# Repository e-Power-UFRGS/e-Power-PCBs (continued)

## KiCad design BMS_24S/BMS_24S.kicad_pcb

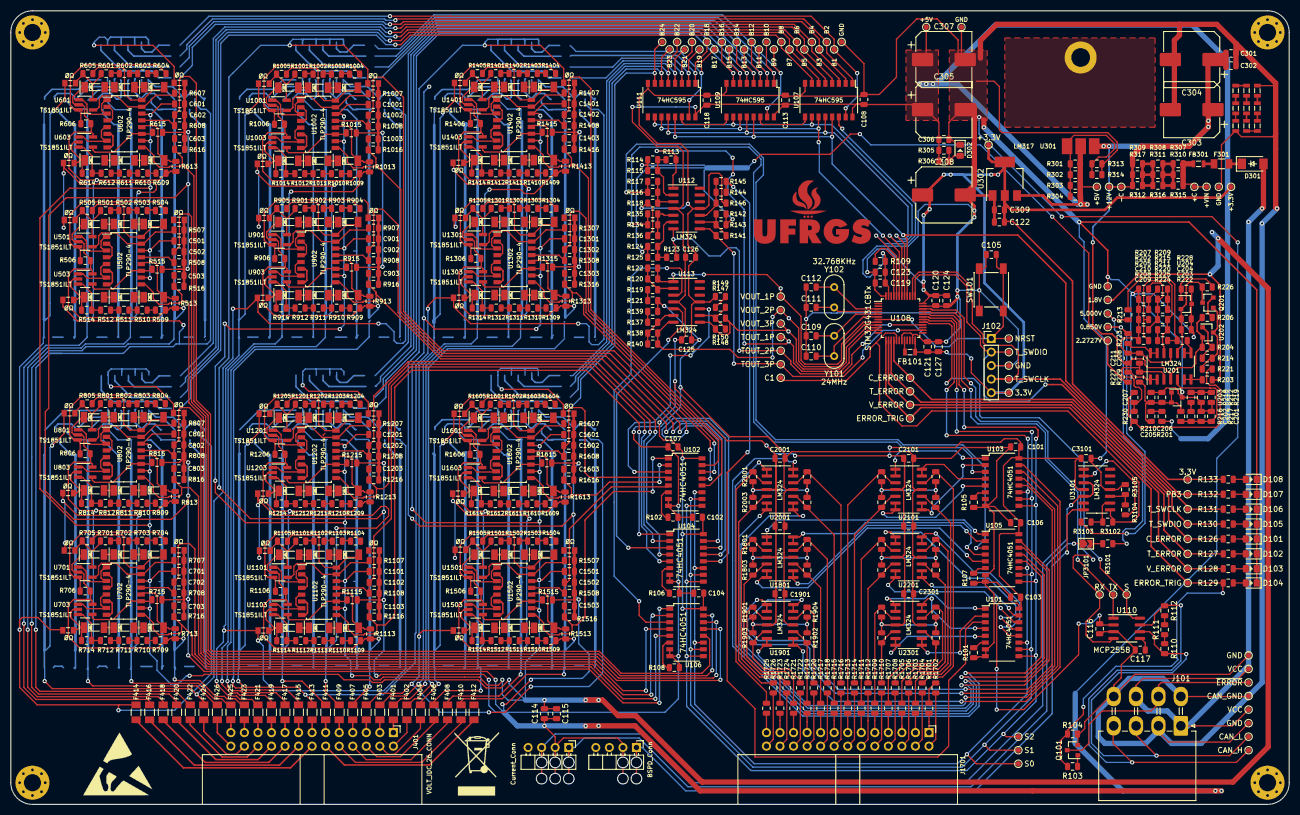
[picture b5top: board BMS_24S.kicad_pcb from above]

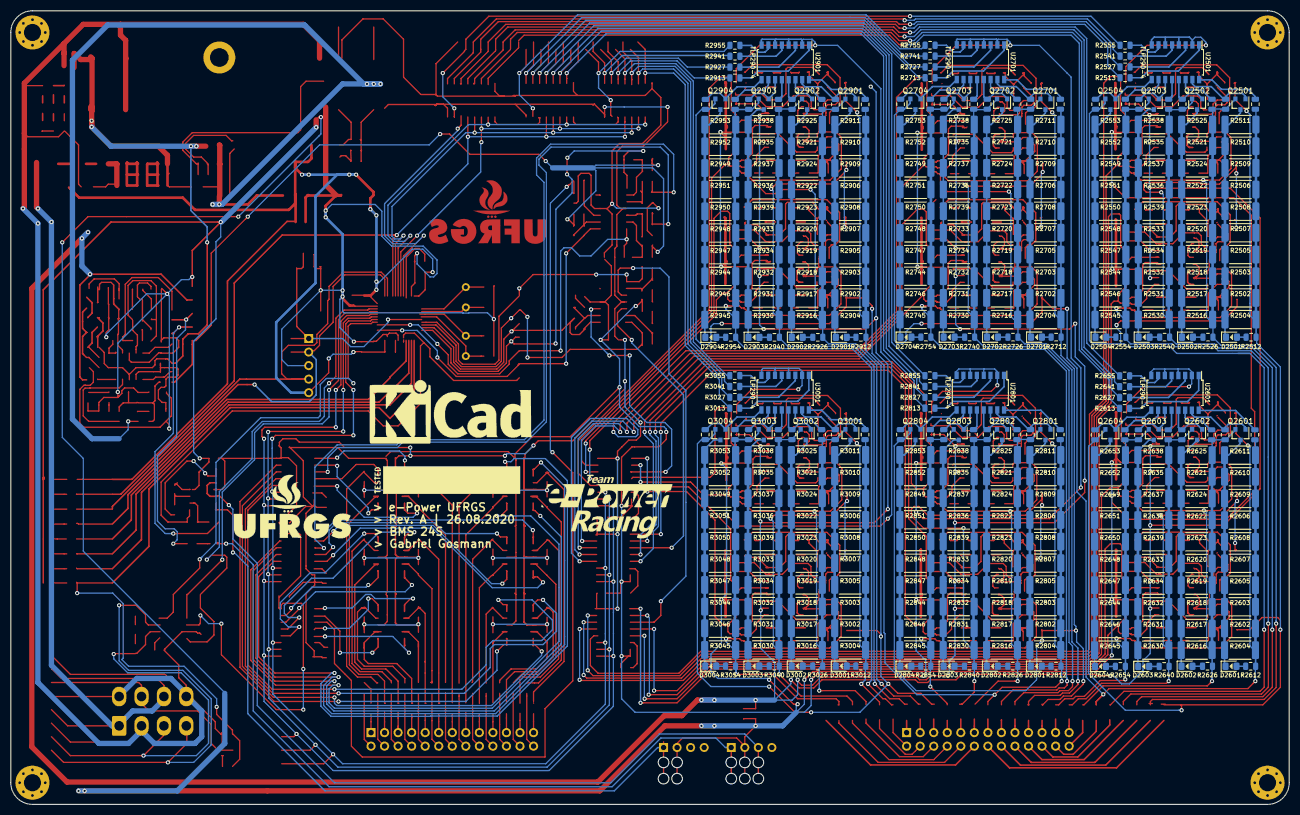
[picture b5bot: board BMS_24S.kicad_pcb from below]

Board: 2 copper layers, 239.8 x 148.8 mm, 1142 parts (393 on the bottom side), 658 nets.

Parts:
C101, C102, C103, C104, C105, C106, C107, C108, C113, C115, C116, C117, C118, C119, C120, C121, C122, C125, C126, C201, C204, C206, C207, C209, C211, C301, C306, C309, C501, C502, C503, C601, C602, C603, C701, C702, C703, C801, C802, C803, C901, C902, C903, C1001, C1002, C1003, C1101, C1102, C1103, C1201, C1202, C1203, C1301, C1302, C1303, C1401, C1402, C1403, C1501, C1502, C1503, C1601, C1602, C1603, C1801, C1901, C2001, C2101, C2201, C2301, C3101: 100nF; C_0805_2012Metric
C109, C110: 12pF; C_0805_2012Metric
C111, C112: 100pF; C_0805_2012Metric
C114, C123, C124, C127, C202, C203, C205, C208, C210, C302: 10uF; C_0805_2012Metric
C303, C304, C305, C307, C308: 220uF; CP_Elec_10x10
D101, D102, D103, D104, D105, D106, D107, D108, D302, D2501, D2502, D2503, D2504, D2601, D2602, D2603, D2604, D2701, D2702, D2703, D2704, D2801, D2802, D2803, D2804, D2901, D2902, D2903, D2904, D3001, D3002, D3003, D3004: LED; LED_0805_1.15x1.40mm_HandSolder
D301: SS54HF; DO-214AC
D501, D502, D503, D504, D505, D506, D601, D602, D603, D604, D605, D606, D701, D702, D703, D704, D705, D706, D801, D802, D803, D804, D805, D806, D901, D902, D903, D904, D905, D906, D1001, D1002, D1003, D1004, D1005, D1006, D1101, D1102, D1103, D1104, D1105, D1106, D1201, D1202, D1203, D1204, D1205, D1206, D1301, D1302, D1303, D1304, D1305, D1306, D1401, D1402, D1403, D1404, D1405, D1406, D1501, D1502, D1503, D1504, D1505, D1506, D1601, D1602, D1603, D1604, D1605, D1606: LL4148; SOD-80
F301: Fuse_1206; FUSE_1206_3216Metric
F401, F402, F403, F404, F405, F406, F407, F408, F409, F410, F411, F412, F413, F414, F415, F416, F417, F418, F419, F420, F421, F422, F423, F424, F425, F426: Fuse; FUSE_1206_3216Metric
FB101, FB301, FB302, FB303, FB304, FB305, FB306, FB307, FB308, FB309, FB310: Ferrite_Bead; FB_0805_2012Metric
G101: Logo_UFRGS_Large; Logo_UFRGS_22.0x12.0mm_Mask
G102: Logo_e-Power_Large; Logo_e-Power_22.8x12.0mm_SilkS
G103: Logo_UFRGS_Large; Logo_UFRGS_22.0x12.0mm_SilkS
G104: SYM_LASER_Large; WEEE-Logo_8.4x12mm_SilkScreen
G105: SYM_LASER_Large; KiCad-Logo_12mm_SilkScreen
G106: SYM_ESD_Large; ESD-Logo_13.2x12mm_SilkScreen
H101, H102, H103, H104: GND; MountingHole_3.2mm_M3_Pad_Via
J101: Conn_01x08_Male; Molex_Mini-Fit_Jr_2x04_P4.20mm_Horizontal
J102: ST-LINK; PinHeader_1x05_P2.54mm_Vertical
J401: VOLT_IDC_26_CONN; IDC-Header_2x13_P2.54mm_Horizontal
J1701: TEMP_IDC_26_CONN; IDC-Header_2x13_P2.54mm_Horizontal
J3101: Current_Conn; PinHeader_1x04_P2.54mm_Horizontal
J3102: BSPD_Conn; PinHeader_1x04_P2.54mm_Horizontal
JP501, JP502, JP503, JP601, JP602, JP603, JP701, JP702, JP703, JP801, JP802, JP803, JP901, JP902, JP903, JP1001, JP1002, JP1003, JP1101, JP1102, JP1103, JP1201, JP1202, JP1203, JP1301, JP1302, JP1303, JP1401, JP1402, JP1403, JP1501, JP1502, JP1503, JP1601, JP1602, JP1603: 0R; zero_ohm_resistor_0805
JP3101: Jumper; SolderJumper-2_P1.3mm_Open_TrianglePad1.0x1.5mm
Q101: MMBT3904; SOT-23
Q201: MMBT5401; SOT-23
Q2501, Q2502, Q2503, Q2504, Q2601, Q2602, Q2603, Q2604, Q2701, Q2702, Q2703, Q2704, Q2801, Q2802, Q2803, Q2804, Q2901, Q2902, Q2903, Q2904, Q3001, Q3002, Q3003, Q3004: Si2302DS; SOT-23
R101, R102, R103, R105, R106, R107, R108, R119, R121, R126, R127, R128, R129, R130, R131, R132, R133, R137, R139, R147, R149, R202, R204, R206, R208, R212, R214, R215, R216, R217, R218, R219, R221, R225, R226, R228, R229, R301, R302, R303, R305, R306, R313, R501, R502, R503, R504, R505, R506, R507, R508, R509, R510, R511, R512, R513, R514, R515, R516, R601, R602, R603, R604, R605, R606, R607, R608, R609, R610, R611, R612, R613, R614, R615, R616, R701, R702, R703, R704, R705, R706, R707, R708, R709, R710, R711, R712, R713, R714, R715, R716, R801, R802, R803, R804, R805, R806, R807, R808, R809, R810, R811, R812, R813, R814, R815, R816, R901, R902, R903, R904, R905, R906, R907, R908, R909, R910, R911, R912, R913, R914, R915, R916, R1001, R1002, R1003, R1004, R1005, R1006, R1007, R1008, R1009, R1010, R1011, R1012, R1013, R1014, R1015, R1016, R1101, R1102, R1103, R1104, R1105, R1106, R1107, R1108, R1109, R1110, R1111, R1112, R1113, R1114, R1115, R1116, R1201, R1202, R1203, R1204, R1205, R1206, R1207, R1208, R1209, R1210, R1211, R1212, R1213, R1214, R1215, R1216, R1301, R1302, R1303, R1304, R1305, R1306, R1307, R1308, R1309, R1310, R1311, R1312, R1313, R1314, R1315, R1316, R1401, R1402, R1403, R1404, R1405, R1406, R1407, R1408, R1409, R1410, R1411, R1412, R1413, R1414, R1415, R1416, R1501, R1502, R1503, R1504, R1505, R1506, R1507, R1508, R1509, R1510, R1511, R1512, R1513, R1514, R1515, R1516, R1601, R1602, R1603, R1604, R1605, R1606, R1607, R1608, R1609, R1610, R1611, R1612, R1613, R1614, R1615, R1616, R1801, R1802, R1803, R1804, R1901, R1902, R1903, R1904, R2001, R2002, R2003, R2004, R2101, R2102, R2103, R2104, R2201, R2202, R2203, R2204, R2301, R2302, R2303, R2304, R2501, R2515, R2529, R2543, R2601, R2615, R2629, R2643, R2701, R2715, R2729, R2743, R2801, R2815, R2829, R2843, R2901, R2915, R2929, R2943, R3001, R3015, R3029, R3043: 1K; R_0805_2012Metric
R104, R109, R113, R114, R115, R116, R117, R118, R120, R122, R123, R124, R125, R134, R135, R136, R138, R140, R141, R142, R143, R144, R145, R146, R148, R150, R224, R230, R2514, R2528, R2542, R2556, R2614, R2628, R2642, R2656, R2714, R2728, R2742, R2756, R2814, R2828, R2842, R2856, R2914, R2928, R2942, R2956, R3014, R3028, R3042, R3056, R3102, R3103, R3104, R3105: 10K; R_0805_2012Metric
R110, R201, R210: 100R; R_0805_2012Metric
R111, R112: 10R; R_0805_2012Metric
R203, R209, R213, R220, R222, R223, R227, R1701, R1702, R1703, R1704, R1705, R1706, R1707, R1708, R1709, R1710, R1711, R1712, R1713, R1714, R1715, R1716, R1717, R1718, R1719, R1720, R1721, R1722, R1723, R1724, R1725, R1726, R3101: 0R; R_0805_2012Metric
R205, R207, R211: 100K; R_0805_2012Metric
R304, R314: ADJ; R_0805_2012Metric
R307, R308, R309, R310, R311, R312, R315, R316, R317: 1R; R_0805_2012Metric
R2502, R2503, R2504, R2505, R2506, R2507, R2508, R2509, R2510, R2511, R2516, R2517, R2518, R2519, R2520, R2521, R2522, R2523, R2524, R2525, R2530, R2531, R2532, R2533, R2534, R2535, R2536, R2537, R2538, R2539, R2544, R2545, R2546, R2547, R2548, R2549, R2550, R2551, R2552, R2553, R2602, R2603, R2604, R2605, R2606, R2607, R2608, R2609, R2610, R2611, R2616, R2617, R2618, R2619, R2620, R2621, R2622, R2623, R2624, R2625, R2630, R2631, R2632, R2633, R2634, R2635, R2636, R2637, R2638, R2639, R2644, R2645, R2646, R2647, R2648, R2649, R2650, R2651, R2652, R2653, R2702, R2703, R2704, R2705, R2706, R2707, R2708, R2709, R2710, R2711, R2716, R2717, R2718, R2719, R2720, R2721, R2722, R2723, R2724, R2725, R2730, R2731, R2732, R2733, R2734, R2735, R2736, R2737, R2738, R2739, R2744, R2745, R2746, R2747, R2748, R2749, R2750, R2751, R2752, R2753, R2802, R2803, R2804, R2805, R2806, R2807, R2808, R2809, R2810, R2811, R2816, R2817, R2818, R2819, R2820, R2821, R2822, R2823, R2824, R2825, R2830, R2831, R2832, R2833, R2834, R2835, R2836, R2837, R2838, R2839, R2844, R2845, R2846, R2847, R2848, R2849, R2850, R2851, R2852, R2853, R2902, R2903, R2904, R2905, R2906, R2907, R2908, R2909, R2910, R2911, R2916, R2917, R2918, R2919, R2920, R2921, R2922, R2923, R2924, R2925, R2930, R2931, R2932, R2933, R2934, R2935, R2936, R2937, R2938, R2939, R2944, R2945, R2946, R2947, R2948, R2949, R2950, R2951, R2952, R2953, R3002, R3003, R3004, R3005, R3006, R3007, R3008, R3009, R3010, R3011, R3016, R3017, R3018, R3019, R3020, R3021, R3022, R3023, R3024, R3025, R3030, R3031, R3032, R3033, R3034, R3035, R3036, R3037, R3038, R3039, R3044, R3045, R3046, R3047, R3048, R3049, R3050, R3051, R3052, R3053: 100R; R_2512_6332Metric
R2512, R2513, R2526, R2527, R2540, R2541, R2554, R2555, R2612, R2613, R2626, R2627, R2640, R2641, R2654, R2655, R2712, R2713, R2726, R2727, R2740, R2741, R2754, R2755, R2812, R2813, R2826, R2827, R2840, R2841, R2854, R2855, R2912, R2913, R2926, R2927, R2940, R2941, R2954, R2955, R3012, R3013, R3026, R3027, R3040, R3041, R3054, R3055: 330R; R_0805_2012Metric
SW101: SW_Push; SW_Push_1P1T_NO_6x6mm_H9.5mm
TP101: B1; TestPoint_Pad_D1.0mm
TP102: B2; TestPoint_Pad_D1.0mm
TP103: B3; TestPoint_Pad_D1.0mm
TP104: B4; TestPoint_Pad_D1.0mm
TP105: B5; TestPoint_Pad_D1.0mm
TP106: B6; TestPoint_Pad_D1.0mm
TP107: B7; TestPoint_Pad_D1.0mm
TP108: B8; TestPoint_Pad_D1.0mm
TP109: B9; TestPoint_Pad_D1.0mm
TP110: B10; TestPoint_Pad_D1.0mm
TP111: B11; TestPoint_Pad_D1.0mm
TP112: B12; TestPoint_Pad_D1.0mm
TP113: B13; TestPoint_Pad_D1.0mm
TP114: B14; TestPoint_Pad_D1.0mm
TP115: B15; TestPoint_Pad_D1.0mm
TP116: B16; TestPoint_Pad_D1.0mm
TP117: B17; TestPoint_Pad_D1.0mm
TP118: B18; TestPoint_Pad_D1.0mm
TP119: B19; TestPoint_Pad_D1.0mm
TP120: B20; TestPoint_Pad_D1.0mm
TP121: B21; TestPoint_Pad_D1.0mm
TP122: B22; TestPoint_Pad_D1.0mm
TP123: B23; TestPoint_Pad_D1.0mm
TP124: B24; TestPoint_Pad_D1.0mm
TP125, TP127, TP133, TP138, TP203, TP309, TP310: GND; TestPoint_Pad_D1.0mm
TP126, TP132: VCC; TestPoint_Pad_D1.0mm
TP128: CAN_L; TestPoint_Pad_D1.0mm
TP129: CAN_H; TestPoint_Pad_D1.0mm
TP130: CAN_GND; TestPoint_Pad_D1.0mm
TP131: ~ERROR; TestPoint_Pad_D1.0mm
TP134, TP161: T_SWCLK; TestPoint_Pad_D1.0mm
TP135, TP163: 3.3V; TestPoint_Pad_D1.0mm
TP136: NRST; TestPoint_Pad_D1.0mm
TP137, TP160: T_SWDIO; TestPoint_Pad_D1.0mm
TP139: VOUT_1P; TestPoint_Pad_D1.0mm
TP140: VOUT_2P; TestPoint_Pad_D1.0mm
TP141: VOUT_3P; TestPoint_Pad_D1.0mm
TP142: TOUT_1P; TestPoint_Pad_D1.0mm
TP143, TP159: ERROR_TRIG; TestPoint_Pad_D1.0mm
TP144, TP158: V_ERROR; TestPoint_Pad_D1.0mm
TP145, TP157: T_ERROR; TestPoint_Pad_D1.0mm
TP146, TP156: C_ERROR; TestPoint_Pad_D1.0mm
TP147: C1; TestPoint_Pad_D1.0mm
TP148: S; TestPoint_Pad_D1.0mm
TP149: S0; TestPoint_Pad_D1.0mm
TP150: S1; TestPoint_Pad_D1.0mm
TP151: S2; TestPoint_Pad_D1.0mm
TP152: TX; TestPoint_Pad_D1.0mm
TP153: TOUT_3P; TestPoint_Pad_D1.0mm
TP154: RX; TestPoint_Pad_D1.0mm
TP155: TOUT_2P; TestPoint_Pad_D1.0mm
TP162: PB3; TestPoint_Pad_D1.0mm
TP201: 1.8V; TestPoint_Pad_D1.0mm
TP202: 5.000V; TestPoint_Pad_D1.0mm
TP204: 0.850V; TestPoint_Pad_D1.0mm
TP205: 2.2727V; TestPoint_Pad_D1.0mm
TP301: +VIN; TestPoint_Pad_D1.0mm
TP302: +12V; TestPoint_Pad_D1.0mm
TP303, TP304: +5V; TestPoint_Pad_D1.0mm
TP305, TP306: +3.3V; TestPoint_Pad_D1.0mm
TP307: +C; TestPoint_Pad_D1.0mm
TP308: -C; TestPoint_Pad_D1.0mm
U101, U102, U103, U104, U105, U106: 74HC4051; SOP-16_4.4x10.4mm_P1.27mm
U107, U109, U111: 74HC595; SOP-16_4.4x10.4mm_P1.27mm
U108: STM32G431CBTx; LQFP-48_7x7mm_P0.5mm
U110: MCP2558; SOIC-8_3.9x4.9mm_P1.27mm
U112, U113, U201, U1801, U1901, U2001, U2101, U2201, U2301, U3101: LM324; SOIC-14_3.9x8.7mm_P1.27mm
U202, U203, U204: TL431; SOT-23
U301: LM317; TO-220-3_Horizontal_TabDown
U302: AP1117-33; SOT-223-3_TabPin2
U501, U503, U601, U603, U701, U703, U801, U803, U901, U903, U1001, U1003, U1101, U1103, U1201, U1203, U1301, U1303, U1401, U1403, U1501, U1503, U1601, U1603: TS1851ILT; SOT-23-5_HandSoldering
U502, U602, U702, U802, U902, U1002, U1102, U1202, U1302, U1402, U1502, U1602, U2501, U2601, U2701, U2801, U2901, U3001: TLP290-4; SOIC-16_4.55x10.3mm_P1.27mm(TLP290-4)
Y101: 24MHz; Crystal_HC52-6mm_Vertical
Y102: 32.768KHz; Crystal_HC52-6mm_Vertical

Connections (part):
+3V3: C119.1, C120.1, C121.1, C122.1, C123.1, C124.1, C127.1, C308.1, C309.1, FB101.1, J102.5, R133.1, TP135.1, TP163.1, TP305.1, TP306.1, U108.24, U108.36, U108.48, U302.2
+5V: C101.2, C102.2, C103.2, C104.2, C106.2, C107.2, C108.2, C113.2, C116.1, C118.2, C125.1, C126.1, C305.1, C306.1, C307.1, C1801.1, C1901.1, C2001.1, C2101.1, C2201.1, C2301.1, C3101.1, R201.1, R301.1, R302.1, R303.1, R304.1, R305.1, R306.1, R1801.2, R1802.2, R1803.2, R1804.2, R1901.2, R1902.2, R1903.2, R1904.2, R2001.2, R2002.2, R2003.2, R2004.2, R2101.2, R2102.2, R2103.2, R2104.2, R2201.2, R2202.2, R2203.2, R2204.2, R2301.2, R2302.2, R2303.2, R2304.2, TP303.1, TP304.1, U101.16, U102.16, U103.16, U104.16, U105.16, U106.16, U107.16, U109.16, U110.2, U111.16, U112.4, U113.4, U301.2, U302.3, U1801.4, U1901.4, U2001.4, U2101.4, U2201.4, U2301.4, U3101.4
+12V: C211.1, C301.1, C302.1, C303.1, C304.1, R204.2, R206.1, R309.1, R312.1, R317.1, TP302.1, TP308.1, U201.4, U202.2, U301.3
/0.850V: R223.2, R3103.2, TP204.1
/1.8V: C114.1, C115.1, C501.1, C601.1, C701.1, C801.1, C901.1, C1001.1, C1101.1, C1201.1, C1301.1, C1401.1, C1501.1, C1601.1, R203.1, TP201.1, U502.10, U502.14, U602.10, U602.14, U702.10, U702.14, U802.10, U802.14, U902.10, U902.14, U1002.10, U1002.14, U1102.10, U1102.14, U1202.10, U1202.14, U1302.10, U1302.14, U1402.10, U1402.14, U1502.10, U1502.14, U1602.10, U1602.14
/2.2727V: R114.2, R115.2, R124.2, R125.2, R142.2, R143.2, R227.2, TP205.1
/5.000V: R213.2, R3101.1, TP202.1
/B1: R2555.1, TP101.1, U107.15
/B2: R2541.1, TP102.1, U107.1
/B3: R2527.1, TP103.1, U107.2
/B4: R2513.1, TP104.1, U107.3
/B5: R2655.1, TP105.1, U107.4
/B6: R2641.1, TP106.1, U107.5
/B7: R2627.1, TP107.1, U107.6
/B8: R2613.1, TP108.1, U107.7
/B9: R2755.1, TP109.1, U109.15
/B10: R2741.1, TP110.1, U109.1
/B11: R2727.1, TP111.1, U109.2
/B12: R2713.1, TP112.1, U109.3
/B13: R2855.1, TP113.1, U109.4
/B14: R2841.1, TP114.1, U109.5
/B15: R2827.1, TP115.1, U109.6
/B16: R2813.1, TP116.1, U109.7
/B17: R2955.1, TP117.1, U111.15
/B18: R2941.1, TP118.1, U111.1
/B19: R2927.1, TP119.1, U111.2
/B20: R2913.1, TP120.1, U111.3
/B21: R3055.1, TP121.1, U111.4
/B22: R3041.1, TP122.1, U111.5
/B23: R3027.1, TP123.1, U111.6
/B24: R3013.1, TP124.1, U111.7
/C1: R3102.2, TP147.1, U108.17, U3101.8
/CAN_H: J101.4, R112.2, TP129.1, U110.7
/CAN_L: J101.3, R110.2, TP128.1, U110.6
/C_ERROR: R126.1, TP146.1, TP156.1, U108.16
/Current Sensor/BSPD_SIG: J3102.1, U3101.6, U3101.7
/Current Sensor/VCC: J3101.1, JP3101.1
/Current Sensor/VIOUT: J3101.3, U3101.3, U3101.5
/DS: U107.14, U108.44
/ERROR_TRIG: R103.1, R104.1, R129.1, TP143.1, TP159.1, U108.13
/RCLK: U107.12, U108.41, U109.12, U111.12
/RX: TP154.1, U108.34, U110.4
/S: TP148.1, U108.29, U110.8
/S0: TP149.1, U101.11, U102.11, U103.11, U104.11, U105.11, U106.11, U108.30
/S1: TP150.1, U101.10, U102.10, U103.10, U104.10, U105.10, U106.10, U108.31
/S2: TP151.1, U101.9, U102.9, U103.9, U104.9, U105.9, U106.9, U108.32
/SCLK: U107.11, U108.43, U109.11, U111.11
/T1: U105.13, U2001.1, U2001.2
/T2: U105.14, U2001.6, U2001.7
/T3: U105.15, U2001.8, U2001.9
/T4: U105.12, U2001.13, U2001.14
/T5: U105.1, U1801.1, U1801.2
/T6: U105.5, U1801.6, U1801.7
/T7: U105.2, U1801.8, U1801.9
/T8: U105.4, U1801.13, U1801.14
/T9: U103.13, U1901.1, U1901.2
/T10: U103.14, U1901.6, U1901.7
/T11: U103.15, U1901.8, U1901.9
/T12: U103.12, U1901.13, U1901.14
/T13: U103.1, U2101.1, U2101.2
/T14: U103.5, U2101.6, U2101.7
/T15: U103.2, U2101.8, U2101.9
/T16: U103.4, U2101.13, U2101.14
/T17: U101.13, U2201.1, U2201.2
/T18: U101.14, U2201.6, U2201.7
/T19: U101.15, U2201.8, U2201.9
/T20: U101.12, U2201.13, U2201.14
/T21: U101.1, U2301.1, U2301.2
/T22: U101.5, U2301.6, U2301.7
/T23: U101.2, U2301.8, U2301.9
/T24: U101.4, U2301.13, U2301.14
/TOUT_1: R116.2, R117.2, U105.3
/TOUT_1P: R113.1, TP142.1, U108.11, U112.1
/TOUT_2: R134.2, R135.2, U103.3
/TOUT_2P: R123.1, TP155.1, U108.28, U112.7
/TOUT_3: R144.2, R145.2, U101.3
/TOUT_3P: R141.1, TP153.1, U108.26, U112.8
/TX: TP152.1, U108.33, U110.1
/T_ERROR: R127.1, TP145.1, TP157.1, U108.15
/Temperature Sensors/0V: R1701.2, R1702.2
/Temperature Sensors/TS_1: R1725.2, R2001.1, U2001.3
/Temperature Sensors/TS_2: R1726.2, R2003.1, U2001.5
/Temperature Sensors/TS_3: R1715.2, R2002.1, U2001.10
/Temperature Sensors/TS_4: R1716.2, R2004.1, U2001.12
/Temperature Sensors/TS_5: R1723.2, R1801.1, U1801.3
/Temperature Sensors/TS_6: R1724.2, R1803.1, U1801.5
/Temperature Sensors/TS_7: R1717.2, R1802.1, U1801.10
/Temperature Sensors/TS_8: R1718.2, R1804.1, U1801.12
/Temperature Sensors/TS_9: R1721.2, R1901.1, U1901.3
/Temperature Sensors/TS_10: R1722.2, R1903.1, U1901.5
/Temperature Sensors/TS_11: R1719.2, R1902.1, U1901.10
/Temperature Sensors/TS_12: R1720.2, R1904.1, U1901.12
/Temperature Sensors/TS_13: R1713.2, R2101.1, U2101.3
/Temperature Sensors/TS_14: R1714.2, R2103.1, U2101.5
/Temperature Sensors/TS_15: R1703.2, R2102.1, U2101.10
/Temperature Sensors/TS_16: R1704.2, R2104.1, U2101.12
/Temperature Sensors/TS_17: R1711.2, R2201.1, U2201.3
/Temperature Sensors/TS_18: R1712.2, R2203.1, U2201.5
/Temperature Sensors/TS_19: R1705.2, R2202.1, U2201.10
/Temperature Sensors/TS_20: R1706.2, R2204.1, U2201.12
/Temperature Sensors/TS_21: R1709.2, R2301.1, U2301.3
/Temperature Sensors/TS_22: R1710.2, R2303.1, U2301.5
/Temperature Sensors/TS_23: R1707.2, R2302.1, U2301.10
/Temperature Sensors/TS_24: R1708.2, R2304.1, U2301.12
/V1: C503.1, R516.2, U106.13, U502.9
/V2: C502.1, R508.2, U106.14, U502.13
/V3: C603.1, R616.2, U106.15, U602.9
/V4: C602.1, R608.2, U106.12, U602.13
/V5: C703.1, R716.2, U106.1, U702.9
/V6: C702.1, R708.2, U106.5, U702.13
/V7: C803.1, R816.2, U106.2, U802.9
/V8: C802.1, R808.2, U106.4, U802.13
/V9: C903.1, R916.2, U104.13, U902.9
/V10: C902.1, R908.2, U104.14, U902.13
/V11: C1003.1, R1016.2, U104.15, U1002.9
/V12: C1002.1, R1008.2, U104.12, U1002.13
/V13: C1103.1, R1116.2, U104.1, U1102.9
/V14: C1102.1, R1108.2, U104.5, U1102.13
/V15: C1203.1, R1216.2, U104.2, U1202.9
/V16: C1202.1, R1208.2, U104.4, U1202.13
/V17: C1303.1, R1316.2, U102.13, U1302.9
/V18: C1302.1, R1308.2, U102.14, U1302.13
/V19: C1403.1, R1416.2, U102.15, U1402.9
/V20: C1402.1, R1408.2, U102.12, U1402.13
/V21: C1503.1, R1516.2, U102.1, U1502.9
/V22: C1502.1, R1508.2, U102.5, U1502.13
/V23: C1603.1, R1616.2, U102.2, U1602.9
/V24: C1602.1, R1608.2, U102.4, U1602.13
/VCC: D301.2, J101.1, J101.7, TP126.1, TP132.1
/VOUT_1: U106.3, U113.3
/VOUT_1P: R120.1, R122.2, TP139.1, U108.8, U113.1
/VOUT_2: U104.3, U113.5
/VOUT_2P: R138.1, R140.2, TP140.1, U108.9, U113.7
/VOUT_3: U102.3, U113.10
/VOUT_3P: R148.1, R150.2, TP141.1, U108.10, U113.8
/V_ERROR: R128.1, TP144.1, TP158.1, U108.14
/~ERROR: J101.6, Q101.3, TP131.1
/~RESET: U107.10, U108.42, U109.10, U111.10
CELL_1: D503.1, F420.2, Q2503.2, R506.2, R509.2, R513.2, R2542.1, R2543.2, R2544.2, R2545.2, R2546.2, R2547.2, R2548.2, R2549.2, R2550.2, R2551.2, R2552.2, R2553.2, R2554.1, U501.2, U503.5
CELL_2: D606.1, F418.2, JP501.1, JP603.1, Q2502.2, R501.2, R505.2, R614.2, R2528.1, R2529.2, R2530.2, R2531.2, R2532.2, R2533.2, R2534.2, R2535.2, R2536.2, R2537.2, R2538.2, R2539.2, R2540.1, U501.5, U603.2
CELL_3: D603.1, F416.2, Q2501.2, R606.2, R609.2, R613.2, R2514.1, R2515.2, R2516.2, R2517.2, R2518.2, R2519.2, R2520.2, R2521.2, R2522.2, R2523.2, R2524.2, R2525.2, R2526.1, U601.2, U603.5
CELL_4: D706.1, F414.2, JP601.1, JP703.1, Q2604.2, R601.2, R605.2, R714.2, R2501.2, R2502.2, R2503.2, R2504.2, R2505.2, R2506.2, R2507.2, R2508.2, R2509.2, R2510.2, R2511.2, R2512.1, R2656.1, U601.5, U703.2
CELL_5: D703.1, F423.2, Q2603.2, R706.2, R709.2, R713.2, R2642.1, R2643.2, R2644.2, R2645.2, R2646.2, R2647.2, R2648.2, R2649.2, R2650.2, R2651.2, R2652.2, R2653.2, R2654.1, U701.2, U703.5
CELL_6: D806.1, F425.2, JP701.1, JP803.1, Q2602.2, R701.2, R705.2, R814.2, R2628.1, R2629.2, R2630.2, R2631.2, R2632.2, R2633.2, R2634.2, R2635.2, R2636.2, R2637.2, R2638.2, R2639.2, R2640.1, U701.5, U803.2
CELL_7: D803.1, F426.2, Q2601.2, R806.2, R809.2, R813.2, R2614.1, R2615.2, R2616.2, R2617.2, R2618.2, R2619.2, R2620.2, R2621.2, R2622.2, R2623.2, R2624.2, R2625.2, R2626.1, U801.2, U803.5
CELL_8: D906.1, F424.2, JP801.1, JP903.1, Q2704.2, R801.2, R805.2, R914.2, R2601.2, R2602.2, R2603.2, R2604.2, R2605.2, R2606.2, R2607.2, R2608.2, R2609.2, R2610.2, R2611.2, R2612.1, R2756.1, U801.5, U903.2
CELL_9: D903.1, F415.2, Q2703.2, R906.2, R909.2, R913.2, R2742.1, R2743.2, R2744.2, R2745.2, R2746.2, R2747.2, R2748.2, R2749.2, R2750.2, R2751.2, R2752.2, R2753.2, R2754.1, U901.2, U903.5
CELL_10: D1006.1, F417.2, JP901.1, JP1003.1, Q2702.2, R901.2, R905.2, R1014.2, R2728.1, R2729.2, R2730.2, R2731.2, R2732.2, R2733.2, R2734.2, R2735.2, R2736.2, R2737.2, R2738.2, R2739.2, R2740.1, U901.5, U1003.2
CELL_11: D1003.1, F419.2, Q2701.2, R1006.2, R1009.2, R1013.2, R2714.1, R2715.2, R2716.2, R2717.2, R2718.2, R2719.2, R2720.2, R2721.2, R2722.2, R2723.2, R2724.2, R2725.2, R2726.1, U1001.2, U1003.5
CELL_12: D1106.1, F421.2, JP1001.1, JP1103.1, Q2804.2, R1001.2, R1005.2, R1114.2, R2701.2, R2702.2, R2703.2, R2704.2, R2705.2, R2706.2, R2707.2, R2708.2, R2709.2, R2710.2, R2711.2, R2712.1, R2856.1, U1001.5, U1103.2
CELL_13: D1103.1, F407.2, Q2803.2, R1106.2, R1109.2, R1113.2, R2842.1, R2843.2, R2844.2, R2845.2, R2846.2, R2847.2, R2848.2, R2849.2, R2850.2, R2851.2, R2852.2, R2853.2, R2854.1, U1101.2, U1103.5
CELL_14: D1206.1, F409.2, JP1101.1, JP1203.1, Q2802.2, R1101.2, R1105.2, R1214.2, R2828.1, R2829.2, R2830.2, R2831.2, R2832.2, R2833.2, R2834.2, R2835.2, R2836.2, R2837.2, R2838.2, R2839.2, R2840.1, U1101.5, U1203.2
CELL_15: D1203.1, F411.2, Q2801.2, R1206.2, R1209.2, R1213.2, R2814.1, R2815.2, R2816.2, R2817.2, R2818.2, R2819.2, R2820.2, R2821.2, R2822.2, R2823.2, R2824.2, R2825.2, R2826.1, U1201.2, U1203.5
CELL_16: D1306.1, F413.2, JP1201.1, JP1303.1, Q2904.2, R1201.2, R1205.2, R1314.2, R2801.2, R2802.2, R2803.2, R2804.2, R2805.2, R2806.2, R2807.2, R2808.2, R2809.2, R2810.2, R2811.2, R2812.1, R2956.1, U1201.5, U1303.2
CELL_17: D1303.1, F402.2, Q2903.2, R1306.2, R1309.2, R1313.2, R2942.1, R2943.2, R2944.2, R2945.2, R2946.2, R2947.2, R2948.2, R2949.2, R2950.2, R2951.2, R2952.2, R2953.2, R2954.1, U1301.2, U1303.5
CELL_18: D1406.1, F401.2, JP1301.1, JP1403.1, Q2902.2, R1301.2, R1305.2, R1414.2, R2928.1, R2929.2, R2930.2, R2931.2, R2932.2, R2933.2, R2934.2, R2935.2, R2936.2, R2937.2, R2938.2, R2939.2, R2940.1, U1301.5, U1403.2
CELL_19: D1403.1, F403.2, Q2901.2, R1406.2, R1409.2, R1413.2, R2914.1, R2915.2, R2916.2, R2917.2, R2918.2, R2919.2, R2920.2, R2921.2, R2922.2, R2923.2, R2924.2, R2925.2, R2926.1, U1401.2, U1403.5
CELL_20: D1506.1, F405.2, JP1401.1, JP1503.1, Q3004.2, R1401.2, R1405.2, R1514.2, R2901.2, R2902.2, R2903.2, R2904.2, R2905.2, R2906.2, R2907.2, R2908.2, R2909.2, R2910.2, R2911.2, R2912.1, R3056.1, U1401.5, U1503.2
CELL_21: D1503.1, F410.2, Q3003.2, R1506.2, R1509.2, R1513.2, R3042.1, R3043.2, R3044.2, R3045.2, R3046.2, R3047.2, R3048.2, R3049.2, R3050.2, R3051.2, R3052.2, R3053.2, R3054.1, U1501.2, U1503.5
CELL_22: D1606.1, F408.2, JP1501.1, JP1603.1, Q3002.2, R1501.2, R1505.2, R1614.2, R3028.1, R3029.2, R3030.2, R3031.2, R3032.2, R3033.2, R3034.2, R3035.2, R3036.2, R3037.2, R3038.2, R3039.2, R3040.1, U1501.5, U1603.2
CELL_23: D1603.1, F406.2, Q3001.2, R1606.2, R1609.2, R1613.2, R3014.1, R3015.2, R3016.2, R3017.2, R3018.2, R3019.2, R3020.2, R3021.2, R3022.2, R3023.2, R3024.2, R3025.2, R3026.1, U1601.2, U1603.5
CELL_24: F404.2, JP1601.1, R1601.2, R1605.2, R3001.2, R3002.2, R3003.2, R3004.2, R3005.2, R3006.2, R3007.2, R3008.2, R3009.2, R3010.2, R3011.2, R3012.1, U1601.5
CELL_GND: D506.1, F422.2, JP503.1, Q2504.2, R514.2, R2556.1, U503.2
GND: C101.1, C102.1, C103.1, C104.1, C105.2, C106.1, C107.1, C108.1, C109.1, C110.1, C111.1, C112.1, C113.1, C114.2, C115.2, C116.2, C117.2, C118.1, C119.2, C120.2, C121.2, C122.2, C123.2, C124.2, C125.2, C126.2, C127.2, C201.2, C202.2, C203.1, C204.1, C205.2, C206.2, C207.2, C208.2, C209.2, C210.2, C211.2, C301.2, C302.2, C303.2, C304.2, C305.2, C306.2, C307.2, C308.2, C309.2, C501.2, C502.2, C503.2, C601.2, C602.2, C603.2, C701.2, C702.2, C703.2, C801.2, C802.2, C803.2, C901.2, C902.2, C903.2, C1001.2, C1002.2, C1003.2, C1101.2, C1102.2, C1103.2, C1201.2, C1202.2, C1203.2, C1301.2, C1302.2, C1303.2, C1401.2, C1402.2, C1403.2, C1501.2, C1502.2, C1503.2, C1601.2, C1602.2, C1603.2, C1801.2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
NRST: C105.1, J102.1, SW101.2, TP136.1, U108.7
unnamed: C109.2, U108.5, Y101.1
unnamed: C110.2, U108.6, Y101.2
unnamed: C111.2, U108.4, Y102.1
unnamed: C112.2, U108.3, Y102.2
unnamed: C117.1, U110.5
unnamed: C201.1, C202.1, R216.1, R217.2, U201.5
unnamed: C203.2, C204.2, Q201.3, R226.2, U201.10, U204.2
unnamed: C205.1, C206.1, R210.2, R216.2, R229.2, U203.1, U203.2
unnamed: C207.1, C208.1, R229.1, R230.2, U201.3
unnamed: C209.1, C210.1, R220.2, R225.2, U201.12
unnamed: D101.2, R126.2
unnamed: D102.2, R127.2
unnamed: D103.2, R128.2
unnamed: D104.2, R129.2
unnamed: D105.2, R130.2
unnamed: D106.2, R131.2
unnamed: D107.2, R132.2
unnamed: D108.2, R133.2
unnamed: D301.1, F301.2
unnamed: D302.2, R305.2, R306.2
unnamed: D501.1, D502.2
unnamed: D501.2, R505.1, U502.16
unnamed: D502.1, D503.2
unnamed: D504.1, D505.2
unnamed: D504.2, R513.1, U502.12
unnamed: D505.1, D506.2
unnamed: D601.1, D602.2
unnamed: D601.2, R605.1, U602.16
unnamed: D602.1, D603.2
unnamed: D604.1, D605.2
unnamed: D604.2, R613.1, U602.12
unnamed: D605.1, D606.2
unnamed: D701.1, D702.2
unnamed: D701.2, R705.1, U702.16
unnamed: D702.1, D703.2
unnamed: D704.1, D705.2
unnamed: D704.2, R713.1, U702.12
unnamed: D705.1, D706.2
unnamed: D801.1, D802.2
unnamed: D801.2, R805.1, U802.16
unnamed: D802.1, D803.2
unnamed: D804.1, D805.2
unnamed: D804.2, R813.1, U802.12
unnamed: D805.1, D806.2
unnamed: D901.1, D902.2
unnamed: D901.2, R905.1, U902.16
unnamed: D902.1, D903.2
unnamed: D904.1, D905.2
unnamed: D904.2, R913.1, U902.12
unnamed: D905.1, D906.2
unnamed: D1001.1, D1002.2
unnamed: D1001.2, R1005.1, U1002.16
unnamed: D1002.1, D1003.2
unnamed: D1004.1, D1005.2
unnamed: D1004.2, R1013.1, U1002.12
unnamed: D1005.1, D1006.2
unnamed: D1101.1, D1102.2
unnamed: D1101.2, R1105.1, U1102.16
unnamed: D1102.1, D1103.2
unnamed: D1104.1, D1105.2
unnamed: D1104.2, R1113.1, U1102.12
unnamed: D1105.1, D1106.2
unnamed: D1201.1, D1202.2
unnamed: D1201.2, R1205.1, U1202.16
unnamed: D1202.1, D1203.2
unnamed: D1204.1, D1205.2
unnamed: D1204.2, R1213.1, U1202.12
unnamed: D1205.1, D1206.2
unnamed: D1301.1, D1302.2
unnamed: D1301.2, R1305.1, U1302.16
unnamed: D1302.1, D1303.2
unnamed: D1304.1, D1305.2
unnamed: D1304.2, R1313.1, U1302.12
unnamed: D1305.1, D1306.2
unnamed: D1401.1, D1402.2
unnamed: D1401.2, R1405.1, U1402.16
unnamed: D1402.1, D1403.2
unnamed: D1404.1, D1405.2
unnamed: D1404.2, R1413.1, U1402.12
unnamed: D1405.1, D1406.2
unnamed: D1501.1, D1502.2
unnamed: D1501.2, R1505.1, U1502.16
unnamed: D1502.1, D1503.2
unnamed: D1504.1, D1505.2
unnamed: D1504.2, R1513.1, U1502.12
unnamed: D1505.1, D1506.2
unnamed: D1601.1, D1602.2
unnamed: D1601.2, R1605.1, U1602.16
unnamed: D1602.1, D1603.2
unnamed: D1604.1, D1605.2
unnamed: D1604.2, R1613.1, U1602.12
unnamed: D1605.1, D1606.2
unnamed: D2501.1, Q2501.3, R2502.1, R2503.1, R2504.1, R2505.1, R2506.1, R2507.1, R2508.1, R2509.1, R2510.1, R2511.1
unnamed: D2501.2, R2512.2
unnamed: D2502.1, Q2502.3, R2516.1, R2517.1, R2518.1, R2519.1, R2520.1, R2521.1, R2522.1, R2523.1, R2524.1, R2525.1
unnamed: D2502.2, R2526.2
unnamed: D2503.1, Q2503.3, R2530.1, R2531.1, R2532.1, R2533.1, R2534.1, R2535.1, R2536.1, R2537.1, R2538.1, R2539.1
unnamed: D2503.2, R2540.2
unnamed: D2504.1, Q2504.3, R2544.1, R2545.1, R2546.1, R2547.1, R2548.1, R2549.1, R2550.1, R2551.1, R2552.1, R2553.1
unnamed: D2504.2, R2554.2
unnamed: D2601.1, Q2601.3, R2602.1, R2603.1, R2604.1, R2605.1, R2606.1, R2607.1, R2608.1, R2609.1, R2610.1, R2611.1
unnamed: D2601.2, R2612.2
unnamed: D2602.1, Q2602.3, R2616.1, R2617.1, R2618.1, R2619.1, R2620.1, R2621.1, R2622.1, R2623.1, R2624.1, R2625.1
unnamed: D2602.2, R2626.2
unnamed: D2603.1, Q2603.3, R2630.1, R2631.1, R2632.1, R2633.1, R2634.1, R2635.1, R2636.1, R2637.1, R2638.1, R2639.1
unnamed: D2603.2, R2640.2
unnamed: D2604.1, Q2604.3, R2644.1, R2645.1, R2646.1, R2647.1, R2648.1, R2649.1, R2650.1, R2651.1, R2652.1, R2653.1
unnamed: D2604.2, R2654.2
unnamed: D2701.1, Q2701.3, R2702.1, R2703.1, R2704.1, R2705.1, R2706.1, R2707.1, R2708.1, R2709.1, R2710.1, R2711.1
unnamed: D2701.2, R2712.2
unnamed: D2702.1, Q2702.3, R2716.1, R2717.1, R2718.1, R2719.1, R2720.1, R2721.1, R2722.1, R2723.1, R2724.1, R2725.1
unnamed: D2702.2, R2726.2
unnamed: D2703.1, Q2703.3, R2730.1, R2731.1, R2732.1, R2733.1, R2734.1, R2735.1, R2736.1, R2737.1, R2738.1, R2739.1
unnamed: D2703.2, R2740.2
unnamed: D2704.1, Q2704.3, R2744.1, R2745.1, R2746.1, R2747.1, R2748.1, R2749.1, R2750.1, R2751.1, R2752.1, R2753.1
unnamed: D2704.2, R2754.2
unnamed: D2801.1, Q2801.3, R2802.1, R2803.1, R2804.1, R2805.1, R2806.1, R2807.1, R2808.1, R2809.1, R2810.1, R2811.1
unnamed: D2801.2, R2812.2
unnamed: D2802.1, Q2802.3, R2816.1, R2817.1, R2818.1, R2819.1, R2820.1, R2821.1, R2822.1, R2823.1, R2824.1, R2825.1
unnamed: D2802.2, R2826.2
unnamed: D2803.1, Q2803.3, R2830.1, R2831.1, R2832.1, R2833.1, R2834.1, R2835.1, R2836.1, R2837.1, R2838.1, R2839.1
unnamed: D2803.2, R2840.2
unnamed: D2804.1, Q2804.3, R2844.1, R2845.1, R2846.1, R2847.1, R2848.1, R2849.1, R2850.1, R2851.1, R2852.1, R2853.1
unnamed: D2804.2, R2854.2
unnamed: D2901.1, Q2901.3, R2902.1, R2903.1, R2904.1, R2905.1, R2906.1, R2907.1, R2908.1, R2909.1, R2910.1, R2911.1
unnamed: D2901.2, R2912.2
unnamed: D2902.1, Q2902.3, R2916.1, R2917.1, R2918.1, R2919.1, R2920.1, R2921.1, R2922.1, R2923.1, R2924.1, R2925.1
unnamed: D2902.2, R2926.2
unnamed: D2903.1, Q2903.3, R2930.1, R2931.1, R2932.1, R2933.1, R2934.1, R2935.1, R2936.1, R2937.1, R2938.1, R2939.1
unnamed: D2903.2, R2940.2
unnamed: D2904.1, Q2904.3, R2944.1, R2945.1, R2946.1, R2947.1, R2948.1, R2949.1, R2950.1, R2951.1, R2952.1, R2953.1
unnamed: D2904.2, R2954.2
unnamed: D3001.1, Q3001.3, R3002.1, R3003.1, R3004.1, R3005.1, R3006.1, R3007.1, R3008.1, R3009.1, R3010.1, R3011.1
unnamed: D3001.2, R3012.2
unnamed: D3002.1, Q3002.3, R3016.1, R3017.1, R3018.1, R3019.1, R3020.1, R3021.1, R3022.1, R3023.1, R3024.1, R3025.1
unnamed: D3002.2, R3026.2
unnamed: D3003.1, Q3003.3, R3030.1, R3031.1, R3032.1, R3033.1, R3034.1, R3035.1, R3036.1, R3037.1, R3038.1, R3039.1
unnamed: D3003.2, R3040.2
unnamed: D3004.1, Q3004.3, R3044.1, R3045.1, R3046.1, R3047.1, R3048.1, R3049.1, R3050.1, R3051.1, R3052.1, R3053.1
unnamed: D3004.2, R3054.2
unnamed: F301.1, FB301.2
unnamed: F401.1, J401.1
unnamed: F402.1, J401.2
unnamed: F403.1, J401.3
unnamed: F404.1, J401.4
unnamed: F405.1, J401.5
unnamed: F406.1, J401.6
unnamed: F407.1, J401.7
unnamed: F408.1, J401.8
unnamed: F409.1, J401.9
unnamed: F410.1, J401.10
unnamed: F411.1, J401.11
unnamed: F412.1, J401.12
unnamed: F413.1, J401.13
unnamed: F414.1, J401.14
unnamed: F415.1, J401.15
unnamed: F416.1, J401.16
unnamed: F417.1, J401.17
unnamed: F418.1, J401.18
unnamed: F419.1, J401.19
unnamed: F420.1, J401.20
unnamed: F421.1, J401.21
unnamed: F422.1, J401.22
unnamed: F423.1, J401.23
unnamed: F424.1, J401.24
unnamed: F425.1, J401.25
unnamed: F426.1, J401.26
unnamed: FB301.1, R307.2, R310.2, R315.2, TP301.1, TP307.1
unnamed: FB302.1, FB303.1
unnamed: FB303.2, FB304.2
unnamed: FB304.1, FB305.1
unnamed: FB305.2, FB306.2
unnamed: FB306.1, FB307.1
unnamed: FB307.2, FB308.2
unnamed: FB308.1, FB309.1
unnamed: FB309.2, FB310.2
unnamed: J1701.1, R1701.1
unnamed: J1701.2, R1702.1
unnamed: J1701.3, R1703.1
unnamed: J1701.4, R1704.1
unnamed: J1701.5, R1705.1
unnamed: J1701.6, R1706.1
unnamed: J1701.7, R1707.1
unnamed: J1701.8, R1708.1
unnamed: J1701.9, R1709.1
unnamed: J1701.10, R1710.1
unnamed: J1701.11, R1711.1
unnamed: J1701.12, R1712.1
unnamed: J1701.13, R1713.1
unnamed: J1701.14, R1714.1
unnamed: J1701.15, R1715.1
unnamed: J1701.16, R1716.1
unnamed: J1701.17, R1717.1
unnamed: J1701.18, R1718.1
unnamed: J1701.19, R1719.1
unnamed: J1701.20, R1720.1
unnamed: J1701.21, R1721.1
unnamed: J1701.22, R1722.1
unnamed: J1701.23, R1723.1
unnamed: J1701.24, R1724.1
unnamed: J1701.25, R1725.1
unnamed: J1701.26, R1726.1
unnamed: JP3101.2, R3101.2
unnamed: Q101.1, R103.2
unnamed: Q201.1, R214.2, R221.2, U202.3
unnamed: Q201.2, R206.2
unnamed: Q2501.1, R2514.2, U2501.15
unnamed: Q2502.1, R2528.2, U2501.13
unnamed: Q2503.1, R2542.2, U2501.11
unnamed: Q2504.1, R2556.2, U2501.9
unnamed: Q2601.1, R2614.2, U2601.15
unnamed: Q2602.1, R2628.2, U2601.13
unnamed: Q2603.1, R2642.2, U2601.11
unnamed: Q2604.1, R2656.2, U2601.9
unnamed: Q2701.1, R2714.2, U2701.15
unnamed: Q2702.1, R2728.2, U2701.13
unnamed: Q2703.1, R2742.2, U2701.11
unnamed: Q2704.1, R2756.2, U2701.9
unnamed: Q2801.1, R2814.2, U2801.15
unnamed: Q2802.1, R2828.2, U2801.13
unnamed: Q2803.1, R2842.2, U2801.11
unnamed: Q2804.1, R2856.2, U2801.9
unnamed: Q2901.1, R2914.2, U2901.15
unnamed: Q2902.1, R2928.2, U2901.13
unnamed: Q2903.1, R2942.2, U2901.11
unnamed: Q2904.1, R2956.2, U2901.9
unnamed: Q3001.1, R3014.2, U3001.15
unnamed: Q3002.1, R3028.2, U3001.13
unnamed: Q3003.1, R3042.2, U3001.11
unnamed: Q3004.1, R3056.2, U3001.9
unnamed: R101.2, U101.6
unnamed: R102.2, U102.6
unnamed: R105.2, U103.6
unnamed: R106.2, U104.6
unnamed: R107.2, U105.6
unnamed: R108.2, U106.6
unnamed: R109.1, U108.45
unnamed: R110.1, R111.1
unnamed: R111.2, R112.1
unnamed: R113.2, R114.1, R115.1, U112.2
unnamed: R116.1, R117.1, R118.1, U112.3
unnamed: R119.1, R121.2
unnamed: R119.2, R120.2, R122.1, U113.2
unnamed: R123.2, R124.1, R125.1, U112.6
unnamed: R134.1, R135.1, R136.1, U112.5
unnamed: R137.1, R139.2
unnamed: R137.2, R138.2, R140.1, U113.6
unnamed: R141.2, R142.1, R143.1, U112.9
unnamed: R144.1, R145.1, R146.1, U112.10
unnamed: R147.1, R149.2
unnamed: R147.2, R148.2, R150.1, U113.9
unnamed: R201.2, R210.1
unnamed: R202.1, R205.2, R209.2
unnamed: R203.2, U201.6, U201.7
unnamed: R204.1, R214.1, U202.1
unnamed: R207.2, R208.2, R211.2, R215.2, R220.1
unnamed: R209.1, R211.1, R215.1
unnamed: R212.2, R218.1, R219.2
unnamed: R213.1, R222.2, R224.2
unnamed: R217.1, R218.2
unnamed: R222.1, U201.8, U201.9
unnamed: R223.1, U201.13, U201.14
unnamed: R224.1, R225.1
unnamed: R226.1, R228.1, U204.1
unnamed: R227.1, U201.1, U201.2
unnamed: R301.2, R302.2, R303.2, R304.2, R313.1, R314.1, U301.1
unnamed: R307.1, R308.2, R310.1, R311.2, R315.1, R316.2
unnamed: R308.1, R309.2, R311.1, R312.2, R316.1, R317.2
unnamed: R501.1, R502.2
unnamed: R502.1, R503.2
unnamed: R503.1, R504.2
unnamed: R504.1, R506.1, U501.3
unnamed: R507.2, U501.4, U502.15
unnamed: R509.1, R510.2
unnamed: R510.1, R511.2
unnamed: R511.1, R512.2
unnamed: R512.1, R514.1, U503.3
unnamed: R515.2, U502.11, U503.4
unnamed: R601.1, R602.2
unnamed: R602.1, R603.2
unnamed: R603.1, R604.2
unnamed: R604.1, R606.1, U601.3
unnamed: R607.2, U601.4, U602.15
unnamed: R609.1, R610.2
unnamed: R610.1, R611.2
unnamed: R611.1, R612.2
unnamed: R612.1, R614.1, U603.3
unnamed: R615.2, U602.11, U603.4
unnamed: R701.1, R702.2
unnamed: R702.1, R703.2
unnamed: R703.1, R704.2
unnamed: R704.1, R706.1, U701.3
unnamed: R707.2, U701.4, U702.15
unnamed: R709.1, R710.2
unnamed: R710.1, R711.2
unnamed: R711.1, R712.2
unnamed: R712.1, R714.1, U703.3
unnamed: R715.2, U702.11, U703.4
unnamed: R801.1, R802.2
unnamed: R802.1, R803.2
unnamed: R803.1, R804.2
unnamed: R804.1, R806.1, U801.3
unnamed: R807.2, U801.4, U802.15
unnamed: R809.1, R810.2
unnamed: R810.1, R811.2
unnamed: R811.1, R812.2
unnamed: R812.1, R814.1, U803.3
unnamed: R815.2, U802.11, U803.4
unnamed: R901.1, R902.2
unnamed: R902.1, R903.2
unnamed: R903.1, R904.2
unnamed: R904.1, R906.1, U901.3
unnamed: R907.2, U901.4, U902.15
unnamed: R909.1, R910.2
unnamed: R910.1, R911.2
unnamed: R911.1, R912.2
unnamed: R912.1, R914.1, U903.3
unnamed: R915.2, U902.11, U903.4
unnamed: R1001.1, R1002.2
unnamed: R1002.1, R1003.2
unnamed: R1003.1, R1004.2
unnamed: R1004.1, R1006.1, U1001.3
unnamed: R1007.2, U1001.4, U1002.15
unnamed: R1009.1, R1010.2
unnamed: R1010.1, R1011.2
unnamed: R1011.1, R1012.2
unnamed: R1012.1, R1014.1, U1003.3
unnamed: R1015.2, U1002.11, U1003.4
unnamed: R1101.1, R1102.2
unnamed: R1102.1, R1103.2
unnamed: R1103.1, R1104.2
unnamed: R1104.1, R1106.1, U1101.3
unnamed: R1107.2, U1101.4, U1102.15
unnamed: R1109.1, R1110.2
unnamed: R1110.1, R1111.2
unnamed: R1111.1, R1112.2
unnamed: R1112.1, R1114.1, U1103.3
unnamed: R1115.2, U1102.11, U1103.4
unnamed: R1201.1, R1202.2
unnamed: R1202.1, R1203.2
unnamed: R1203.1, R1204.2
unnamed: R1204.1, R1206.1, U1201.3
unnamed: R1207.2, U1201.4, U1202.15
unnamed: R1209.1, R1210.2
unnamed: R1210.1, R1211.2
unnamed: R1211.1, R1212.2
unnamed: R1212.1, R1214.1, U1203.3
unnamed: R1215.2, U1202.11, U1203.4
unnamed: R1301.1, R1302.2
unnamed: R1302.1, R1303.2
unnamed: R1303.1, R1304.2
unnamed: R1304.1, R1306.1, U1301.3
unnamed: R1307.2, U1301.4, U1302.15
unnamed: R1309.1, R1310.2
unnamed: R1310.1, R1311.2
unnamed: R1311.1, R1312.2
unnamed: R1312.1, R1314.1, U1303.3
unnamed: R1315.2, U1302.11, U1303.4
unnamed: R1401.1, R1402.2
unnamed: R1402.1, R1403.2
unnamed: R1403.1, R1404.2
unnamed: R1404.1, R1406.1, U1401.3
unnamed: R1407.2, U1401.4, U1402.15
unnamed: R1409.1, R1410.2
unnamed: R1410.1, R1411.2
unnamed: R1411.1, R1412.2
unnamed: R1412.1, R1414.1, U1403.3
unnamed: R1415.2, U1402.11, U1403.4
unnamed: R1501.1, R1502.2
unnamed: R1502.1, R1503.2
unnamed: R1503.1, R1504.2
unnamed: R1504.1, R1506.1, U1501.3
unnamed: R1507.2, U1501.4, U1502.15
unnamed: R1509.1, R1510.2
unnamed: R1510.1, R1511.2
unnamed: R1511.1, R1512.2
unnamed: R1512.1, R1514.1, U1503.3
unnamed: R1515.2, U1502.11, U1503.4
unnamed: R1601.1, R1602.2
unnamed: R1602.1, R1603.2
unnamed: R1603.1, R1604.2
unnamed: R1604.1, R1606.1, U1601.3
unnamed: R1607.2, U1601.4, U1602.15
unnamed: R1609.1, R1610.2
unnamed: R1610.1, R1611.2
unnamed: R1611.1, R1612.2
unnamed: R1612.1, R1614.1, U1603.3
unnamed: R1615.2, U1602.11, U1603.4
unnamed: R2501.1, U2501.16
unnamed: R2513.2, U2501.1
unnamed: R2515.1, U2501.14
unnamed: R2527.2, U2501.3
unnamed: R2529.1, U2501.12
unnamed: R2541.2, U2501.5
unnamed: R2543.1, U2501.10
unnamed: R2555.2, U2501.7
unnamed: R2601.1, U2601.16
unnamed: R2613.2, U2601.1
unnamed: R2615.1, U2601.14
unnamed: R2627.2, U2601.3
unnamed: R2629.1, U2601.12
unnamed: R2641.2, U2601.5
unnamed: R2643.1, U2601.10
unnamed: R2655.2, U2601.7
unnamed: R2701.1, U2701.16
unnamed: R2713.2, U2701.1
unnamed: R2715.1, U2701.14
unnamed: R2727.2, U2701.3
unnamed: R2729.1, U2701.12
unnamed: R2741.2, U2701.5
unnamed: R2743.1, U2701.10
unnamed: R2755.2, U2701.7
unnamed: R2801.1, U2801.16
unnamed: R2813.2, U2801.1
unnamed: R2815.1, U2801.14
unnamed: R2827.2, U2801.3
unnamed: R2829.1, U2801.12
unnamed: R2841.2, U2801.5
unnamed: R2843.1, U2801.10
unnamed: R2855.2, U2801.7
unnamed: R2901.1, U2901.16
unnamed: R2913.2, U2901.1
unnamed: R2915.1, U2901.14
unnamed: R2927.2, U2901.3
unnamed: R2929.1, U2901.12
unnamed: R2941.2, U2901.5
unnamed: R2943.1, U2901.10
unnamed: R2955.2, U2901.7
unnamed: R3001.1, U3001.16
unnamed: R3013.2, U3001.1
unnamed: R3015.1, U3001.14
unnamed: R3027.2, U3001.3
unnamed: R3029.1, U3001.12
unnamed: R3041.2, U3001.5
unnamed: R3043.1, U3001.10
unnamed: R3055.2, U3001.7
unnamed: R3102.1, R3103.1, U3101.9
unnamed: R3104.1, R3105.2, U3101.10
unnamed: R3104.2, U3101.1, U3101.2
unnamed: U107.9, U109.14
unnamed: U109.9, U111.14
unnamed: U501.1, U502.1, U502.3
unnamed: U502.2, U502.4
unnamed: U502.5, U502.7, U503.1
unnamed: U502.6, U502.8
unnamed: U601.1, U602.1, U602.3
unnamed: U602.2, U602.4
unnamed: U602.5, U602.7, U603.1
unnamed: U602.6, U602.8
unnamed: U701.1, U702.1, U702.3
unnamed: U702.2, U702.4
unnamed: U702.5, U702.7, U703.1
unnamed: U702.6, U702.8
unnamed: U801.1, U802.1, U802.3
unnamed: U802.2, U802.4
unnamed: U802.5, U802.7, U803.1
unnamed: U802.6, U802.8
unnamed: U901.1, U902.1, U902.3
unnamed: U902.2, U902.4
unnamed: U902.5, U902.7, U903.1
unnamed: U902.6, U902.8
unnamed: U1001.1, U1002.1, U1002.3
unnamed: U1002.2, U1002.4
unnamed: U1002.5, U1002.7, U1003.1
unnamed: U1002.6, U1002.8
unnamed: U1101.1, U1102.1, U1102.3
unnamed: U1102.2, U1102.4
unnamed: U1102.5, U1102.7, U1103.1
unnamed: U1102.6, U1102.8
unnamed: U1201.1, U1202.1, U1202.3
unnamed: U1202.2, U1202.4
unnamed: U1202.5, U1202.7, U1203.1
unnamed: U1202.6, U1202.8
unnamed: U1301.1, U1302.1, U1302.3
unnamed: U1302.2, U1302.4
unnamed: U1302.5, U1302.7, U1303.1
unnamed: U1302.6, U1302.8
unnamed: U1401.1, U1402.1, U1402.3
unnamed: U1402.2, U1402.4
unnamed: U1402.5, U1402.7, U1403.1
unnamed: U1402.6, U1402.8
unnamed: U1501.1, U1502.1, U1502.3
unnamed: U1502.2, U1502.4
unnamed: U1502.5, U1502.7, U1503.1
unnamed: U1502.6, U1502.8
unnamed: U1601.1, U1602.1, U1602.3
unnamed: U1602.2, U1602.4
unnamed: U1602.5, U1602.7, U1603.1
unnamed: U1602.6, U1602.8
PB3: R132.1, TP162.1, U107.13, U108.40, U109.13, U111.13
T_SWCLK: J102.4, R131.1, TP134.1, TP161.1, U108.38
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
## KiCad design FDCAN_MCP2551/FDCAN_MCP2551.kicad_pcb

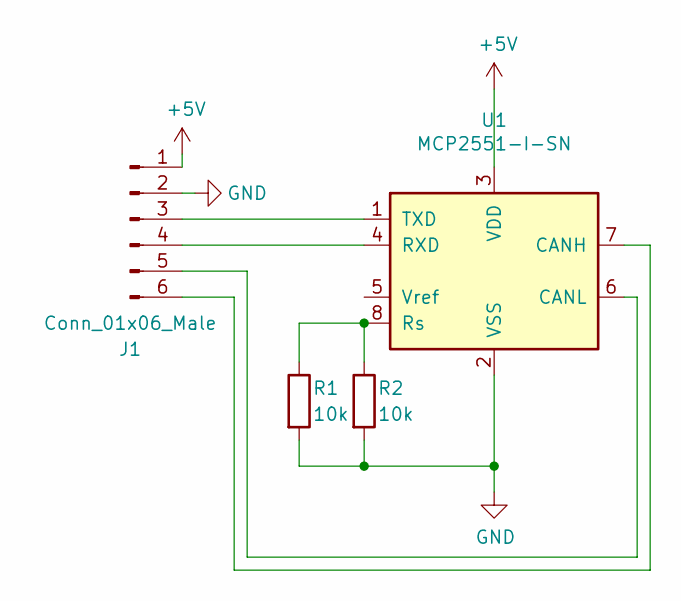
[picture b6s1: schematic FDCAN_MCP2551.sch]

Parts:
J1: Conn_01x06_Male; PinHeader_1x06_P2.54mm_Vertical
R1, R2: 10k; R_0805_2012Metric
U1: MCP2551-I-SN; SOIC-8_3.9x4.9mm_P1.27mm

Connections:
+5V: J1.1, U1.3 (VDD)
GND: J1.2, R1.2, R2.2, U1.2 (VSS)
unnamed: J1.3, U1.1 (TXD)
unnamed: J1.4, U1.4 (RXD)
unnamed: J1.5, U1.6 (CANL)
unnamed: J1.6, U1.7 (CANH)
unnamed: R1.1, R2.1, U1.8 (Rs)

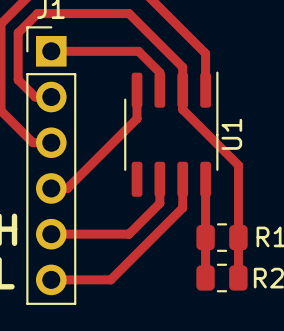
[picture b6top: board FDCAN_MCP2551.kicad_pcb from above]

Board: 2 copper layers, 4 parts (0 on the bottom side), 7 nets.
